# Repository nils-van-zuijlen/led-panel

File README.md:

LED Panel
=========

A LED panel using WS281x LEDs to light up and an RPi to run

---------

It is controllable via OLA (and thus via any of the protocols OLA supports) and a little interface made of buttons with an LCD screen (you can also run it 100% headless).

You can find out more about this project [in the wiki](https://github.com/nils-van-zuijlen/led-panel/wiki)

## Copyright and licensing

This software is copyright (C) 2019 Nils VAN ZUIJLEN

This program is free software: you can redistribute it and/or modify
it under the terms of the GNU General Public License as published by
the Free Software Foundation, either version 3 of the License, or
(at your option) any later version.

This program is distributed in the hope that it will be useful,
but WITHOUT ANY WARRANTY; without even the implied warranty of
MERCHANTABILITY or FITNESS FOR A PARTICULAR PURPOSE.  See the
GNU General Public License for more details.

You should have received [a copy of the GNU General Public License](LICENSE.md)
along with this program.  If not, see <https://www.gnu.org/licenses/>.

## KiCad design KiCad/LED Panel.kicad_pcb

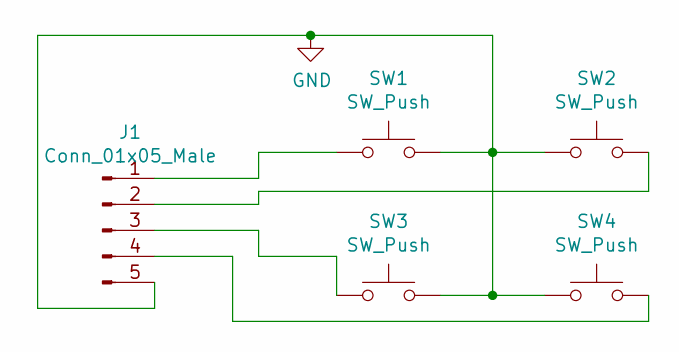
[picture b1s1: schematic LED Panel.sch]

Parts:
J1: Conn_01x05_Male; JST_ACH_BBM05B-ACHSS-A-GAN-ETF_1x05-1MP_P1.20mm_Vertical
SW1, SW2, SW3, SW4: SW_Push; SW_PUSH-12mm_Wuerth-430476085716

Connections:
GND: J1.5, SW1.2, SW2.1, SW3.2, SW4.1
unnamed: J1.1, SW1.1
unnamed: J1.2, SW2.2
unnamed: J1.3, SW3.1
unnamed: J1.4, SW4.2

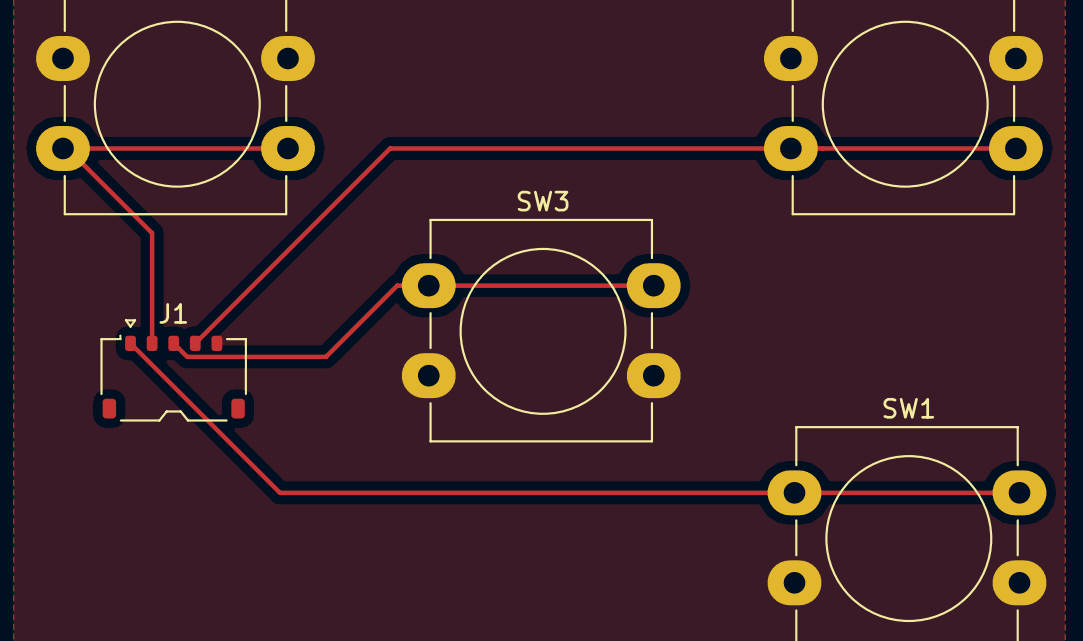
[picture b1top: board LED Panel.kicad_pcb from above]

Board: 2 copper layers, 5 parts (0 on the bottom side), 5 nets.

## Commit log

2019-02-21 Add README
2019-02-21 Add copyright notices
2019-02-21 Add sCAD model
2019-02-21 Add wiki note to README
2019-02-21 Create LICENSE
2019-02-21 Add license to code files
2019-02-21 Edit get_ip_address function to make its output prettier
2019-02-21 Code cleaning
2019-02-21 Style
2019-02-21 Add KiCad model
2019-02-22 Line endings and change LCD library
2019-02-22 make executable
2019-02-22 add gitignore
2019-02-22 change bouncetime
2019-02-22 Fix address indexing
2019-02-22 add status led
2019-02-22 status led
2019-02-22 bouncetime
2019-02-22 Add LCD thread lock
2019-02-22 Add interaction lock
2019-02-22 Add address lock to LEDPanel
2019-02-22 Add macros
2019-02-22 correction
2019-02-22 debug
2019-02-22 I am dumb
2019-02-22 Change the animation
2019-02-22 Improve start and stop of macros
2019-02-22 Update electronic model
2019-02-22 Update step duration
2019-02-22 bugfix
